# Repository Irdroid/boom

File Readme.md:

**Boom! Hat Garage Door Opener for RPI Zero by Irdroid**

**Introduction** 

Boom Hat is a Garage Door Opener HAT for Raspberry Pi Zero, featuring one opto isolated digital output, wired to GPIO17 of the Raspberry Pi Zero, a DC-DC step down converted for powering the raspberry Pi from external DC power source, Terminal blocks for ease of installation. double size header to fit on top of a standard enclosure for Raspberry Pi Zero.

We are living in a Internet-Of-Things era, despite that fact many of the garage door manufacturers are still delivering motorized garage doors with a single option for remote control, using a battery powered RF remote controls, or they are charging decent amount of money for gettting a “Conected” garage door. In addition if you loose the remote control, supplied from the door manufacturer you will have to pay them at least 30 EUR for new one. Boom! is a workaround for these complications as it provides alternative way for controlling your door without the need for physical access cards,remote controls or keys .

Boom! has the ability to tap-in to existing garage door controllers and safely control the garage door via SSH , using a raspberry Pi Zero and one GPIO.

The Boom! Hat for raspberry pi zero has a built in DC-DC step down convertor, that allows you to power up the Pi directly from the DC power source of the Garage door controller. It also has one optically isolated digital output for controlling the garage door from its built-in NO contact (AUX contact)

**Features:**
- 1 Opto isolated Digital Output
- DC-DC step down converter for powering the RPI Zero
- Block terminals for ease of installation
- Double size pin header to fit the hat on top of a standard RPI Zero enclosure

**Example Application:**
- Garage Door Opener
- RFID Gate Opener / as additional feature

**How It works?**

The boom hat has one opto isolated digital output wired to RPI ZERO GPIO17, controlling that GPIO via a shell script or any other means will control the output state of the 4N35 optron.

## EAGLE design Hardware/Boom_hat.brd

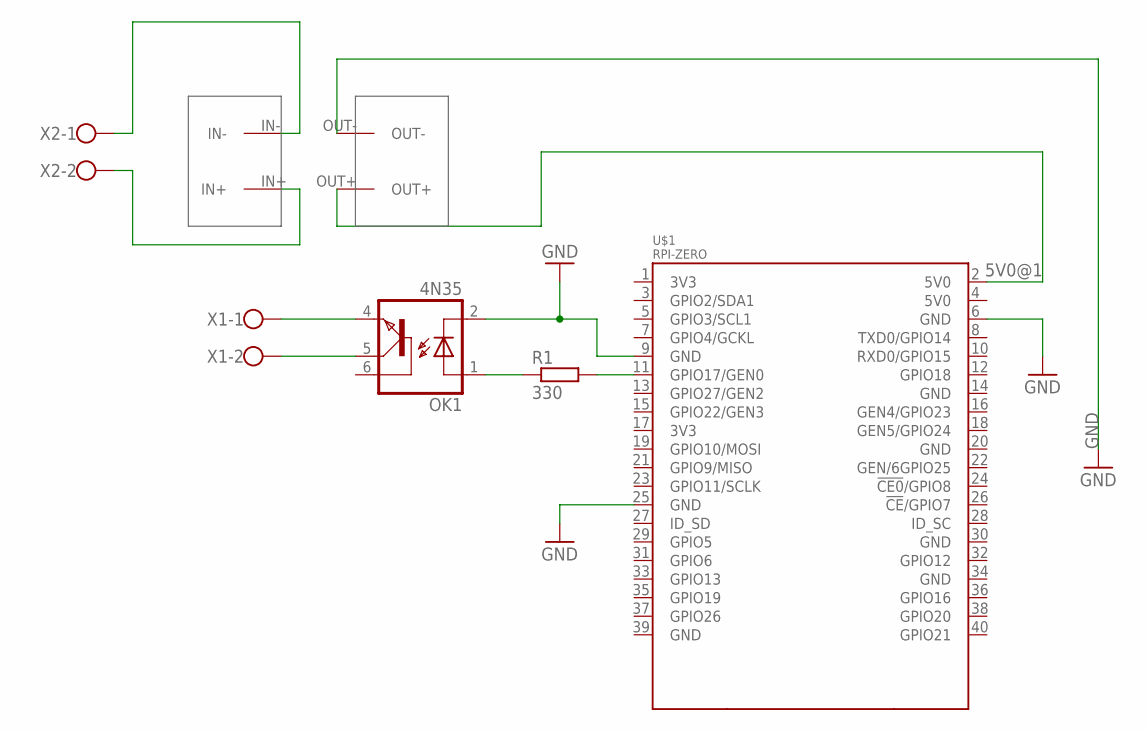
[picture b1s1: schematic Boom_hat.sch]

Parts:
OK1: 4N35; DIL06
R1: 330; 0204/5
U$1: RPI-ZERO; RASPBERRYPI_BASTELSTUBE_V13_RASPI_BOARD_B+_FULL
U$2: DCDC
X1, X2: W237-102

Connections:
5V0@1: U$1.2 (5V0), U$2.OUT+
GND: OK1.2 (C), U$1.6 (GND), U$1.9 (GND), U$1.25 (GND), U$2.OUT-
unnamed: R1.2, U$1.11 (GPIO17/GEN0)
unnamed: OK1.1 (A), R1.1
unnamed: OK1.5 (COL), X1.2
unnamed: OK1.4 (EMI), X1.1
unnamed: U$2.IN-, X2.1
unnamed: U$2.IN+, X2.2

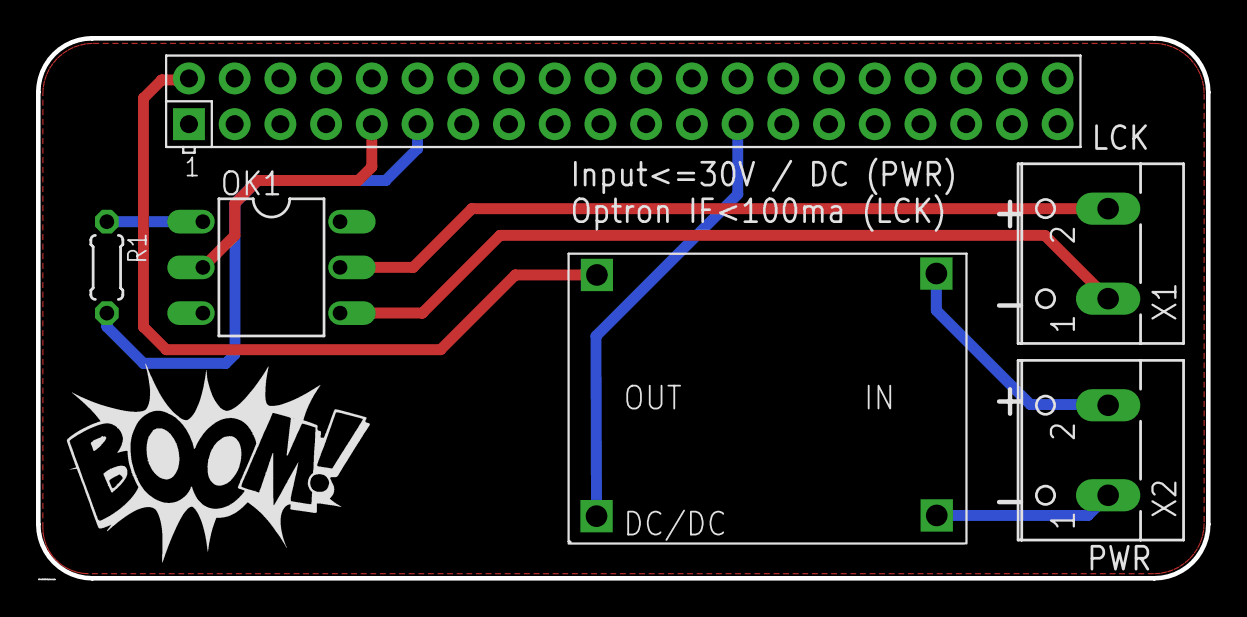
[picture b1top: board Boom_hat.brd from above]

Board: 2 copper layers, 65.0 x 30.0 mm, 6 parts (0 on the bottom side), 8 nets.

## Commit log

2021-12-10 updated readme
    updated readme
